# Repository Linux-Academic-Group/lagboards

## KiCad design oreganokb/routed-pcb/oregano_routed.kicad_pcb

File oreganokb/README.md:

# Oregano

[Upstream repo](https://github.com/pwlsp/oreganokb)

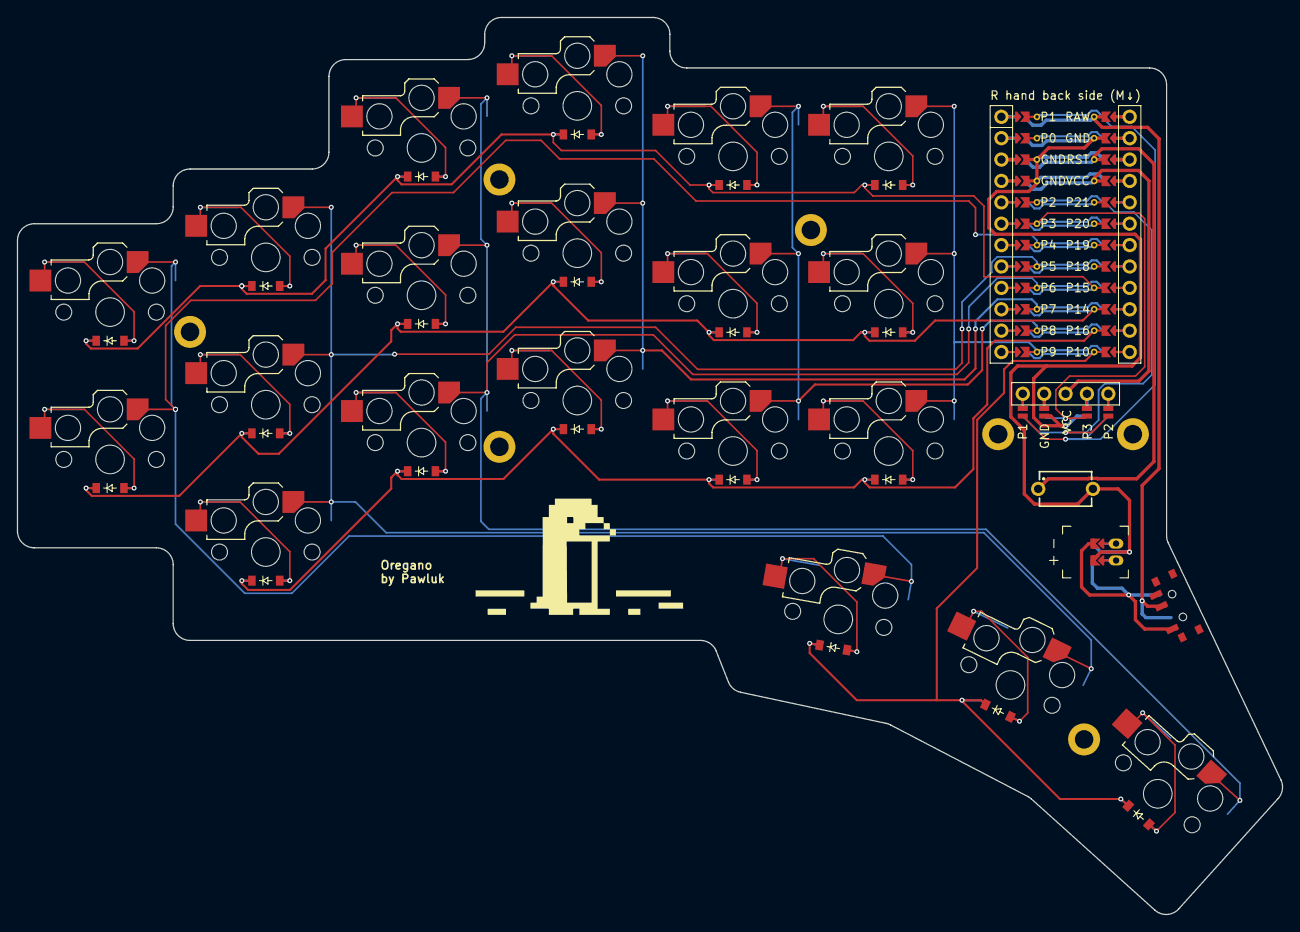
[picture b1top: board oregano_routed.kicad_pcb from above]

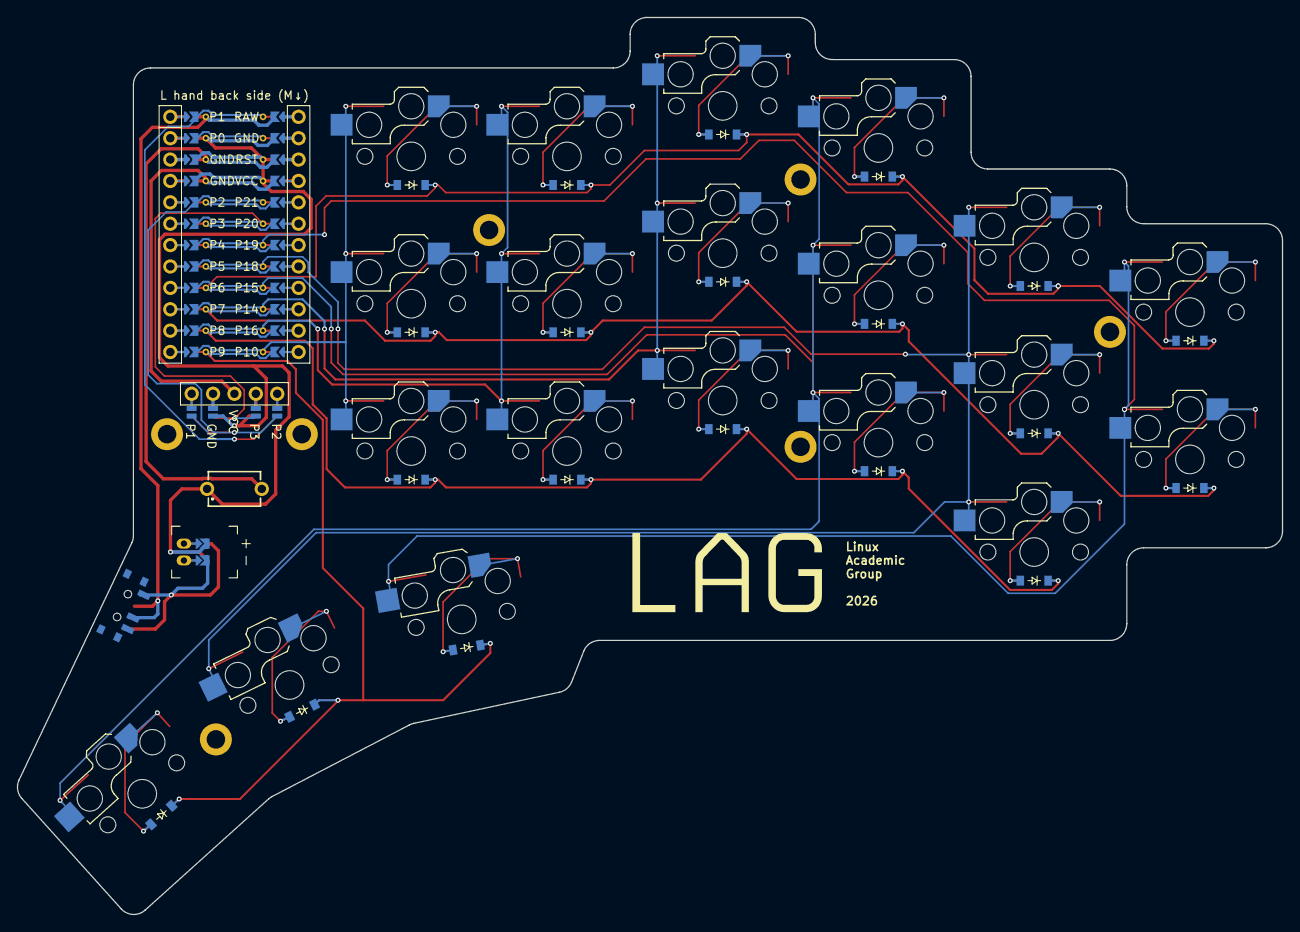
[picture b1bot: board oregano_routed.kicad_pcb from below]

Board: 2 copper layers, 150.3 x 106.6 mm, 52 parts (20 on the bottom side), 44 nets.

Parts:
D1, D2, D3, D4, D5, D6, D7, D8, D9, D10, D11, D12, D13, D14, D15, D16, D17, D18, D19, D20: diode_tht_sod123
DISP1: display_nice_view
H1, H2, H3, H4, H5, H6, H7: mounting_hole_plated
JST1: battery_connector_jst_ph_2
MCU1: mcu_supermini_nrf52840
S1, S2, S3, S4, S5, S6, S7, S8, S9, S10, S11, S12, S13, S14, S15, S16, S17, S18, S19, S20: switch_choc_v1_v2
S21: 434121025816
T1: SW_SPDT_PCM12

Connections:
BAT_P: JST1.1, T1.1
DISP1_1: DISP1.1, DISP1.14, DISP1.27
DISP1_2: DISP1.2, DISP1.15, DISP1.26
DISP1_4: DISP1.4, DISP1.16, DISP1.25
DISP1_5: DISP1.5, DISP1.17, DISP1.24
GND: DISP1.11, DISP1.21, JST1.2, MCU1.102, MCU1.121, MCU1.122, S21.2
JST1_1: JST1.11, JST1.21, JST1.31
JST1_2: JST1.12, JST1.22, JST1.32
P1: DISP1.10, DISP1.20, MCU1.124
P2: DISP1.13, DISP1.23, MCU1.120
P3: DISP1.12, DISP1.22, MCU1.119
P4: MCU1.118, S1.1, S1.2, S2.1, S2.2, S18.1, S18.2
P5: MCU1.117, S3.1, S3.2, S4.1, S4.2, S5.1, S5.2, S19.1, S19.2
P6: MCU1.116, S6.1, S6.2, S7.1, S7.2, S8.1, S8.2, S20.1, S20.2
P7: MCU1.115, S9.1, S9.2, S10.1, S10.2, S11.1, S11.2
P8: MCU1.114, S12.1, S12.2, S13.1, S13.2, S14.1, S14.2
P9: MCU1.113, S15.1, S15.2, S16.1, S16.2, S17.1, S17.2
P10: D18.1, D19.1, D20.1, MCU1.112
P14: D1.1, D4.1, D7.1, D10.1, D13.1, D16.1, MCU1.110
P15: D2.1, D5.1, D8.1, D11.1, D14.1, D17.1, MCU1.109
P16: D3.1, D6.1, D9.1, D12.1, D15.1, MCU1.111
RAW: MCU1.101, T1.2
RST: MCU1.103, S21.1
VCC: DISP1.3, MCU1.104
far_row: D20.2, S20.1, S20.2
home_row: D19.2, S19.1, S19.2
index_bottom: D12.2, S12.1, S12.2
index_home: D13.2, S13.1, S13.2
index_top: D14.2, S14.1, S14.2
inner_bottom: D15.2, S15.1, S15.2
inner_home: D16.2, S16.1, S16.2
inner_top: D17.2, S17.1, S17.2
middle_bottom: D9.2, S9.1, S9.2
middle_home: D10.2, S10.1, S10.2
middle_top: D11.2, S11.1, S11.2
near_row: D18.2, S18.1, S18.2
outer_home: D1.2, S1.1, S1.2
outer_top: D2.2, S2.1, S2.2
pinky_bottom: D3.2, S3.1, S3.2
pinky_home: D4.2, S4.1, S4.2
pinky_top: D5.2, S5.1, S5.2
ring_bottom: D6.2, S6.1, S6.2
ring_home: D7.2, S7.1, S7.2
ring_top: D8.2, S8.1, S8.2

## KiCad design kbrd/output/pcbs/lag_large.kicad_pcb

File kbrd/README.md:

```bash
ergogen . && flatpak --command=pcbnew run org.kicad.KiCad output/pcbs/lag_large.kicad_pcb                                                                                   
```

```
 encoder | 1    RAW | 
 encoder | 0    GND |
         | GND  RST |
         | GND  VCC |
     SDA | 2     21 | analog
     SCL | 3     20 | analog
   COL_5 | 4     19 | analog
   COL_4 | 5     18 | ROW_4
   COL_3 | 6     15 | ROW_3
   COL_2 | 7     14 | ROW_2
   COL_1 | 8     16 | ROW_1
   COL_0 | 9     10 | ROW_0
```

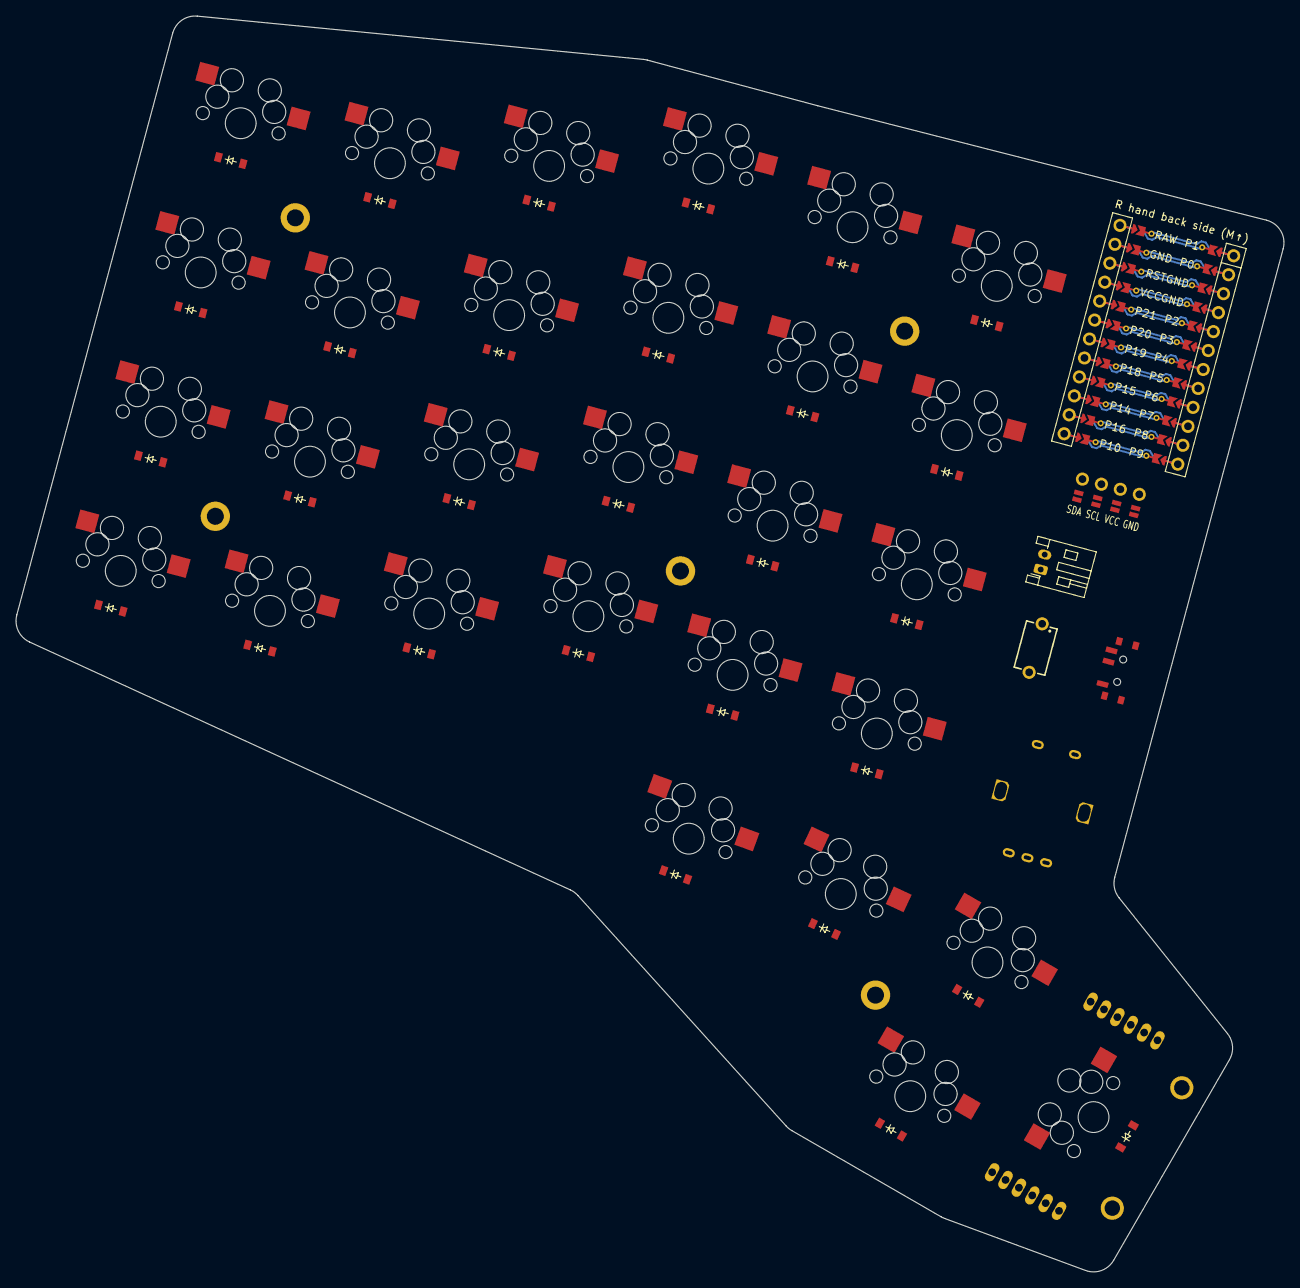
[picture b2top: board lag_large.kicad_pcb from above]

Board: 2 copper layers, 164.2 x 162.6 mm, 72 parts (1 on the bottom side), 57 nets.

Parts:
D1, D2, D3, D4, D5, D6, D7, D8, D9, D10, D11, D12, D13, D14, D15, D16, D17, D18, D19, D20, D21, D22, D23, D24, D25, D26, D27, D28, D29, D30: diode_tht_sod123
DISP1: nice!view
H1, H2, H3, H4, H5: mounting_hole_plated
MCU1: mcu_supermini_nrf52840
RE1: rotary_encoder_ec11_ec12
S1, S2, S3, S4, S5, S6, S7, S8, S9, S10, S11, S12, S13, S14, S15, S16, S17, S18, S19, S20, S21, S22, S23, S24, S25, S26, S27, S28, S29: MX
S30: 434121025816
T1: SW_SPDT_PCM12
XX1, XX2: joystick
_1: JST_PH_S2B-PH-K_1x02_P2.00mm_Horizontal

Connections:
DISP1_1: DISP1.4, DISP1.13, DISP1.20
DISP1_2: DISP1.3, DISP1.12, DISP1.21
DISP1_3: DISP1.2, DISP1.11, DISP1.22
DISP1_4: DISP1.1, DISP1.10, DISP1.23
GND: DISP1.14, DISP1.24, MCU1.103, MCU1.104, MCU1.123, RE1.B, S30.2, XX1.2, XX1.5, XX2.2, XX2.5, _1.1
P0: MCU1.102, RE1.A
P1: MCU1.101, RE1.C
P2: DISP1.17, DISP1.27, MCU1.105
P3: DISP1.16, DISP1.26, MCU1.106
P4: MCU1.107, S1.1, S2.1, S3.1, S4.1, S25.1
P5: MCU1.108, S5.1, S6.1, S7.1, S8.1, S26.1
P6: MCU1.109, S9.1, S10.1, S11.1, S12.1, S28.1
P7: MCU1.110, S13.1, S14.1, S15.1, S16.1, S27.1
P8: MCU1.111, S17.1, S18.1, S19.1, S20.1, S29.1
P9: MCU1.112, RE1.S1, S21.1, S22.1, S23.1, S24.1
P10: D25.1, D26.1, D27.1, D28.1, D29.1, D30.1, MCU1.113
P14: D2.1, D6.1, D10.1, D14.1, D18.1, D22.1, MCU1.115
P15: D3.1, D7.1, D11.1, D15.1, D19.1, D23.1, MCU1.116
P16: D1.1, D5.1, D9.1, D13.1, D17.1, D21.1, MCU1.114
P18: D4.1, D8.1, D12.1, D16.1, D20.1, D24.1, MCU1.117
P19: MCU1.118, XX1.4, XX2.4
P20: MCU1.119, XX1.3, XX2.3
P21: MCU1.120, XX1.6, XX2.6
RAW: MCU1.124, T1.2
RST: MCU1.122, S30.1
VCC: DISP1.15, DISP1.25, MCU1.121, XX1.1, XX2.1
en_s2: D30.2, RE1.S2
index_bottom: D17.2, S17.2
index_home: D18.2, S18.2
index_num: D20.2, S20.2
index_top: D19.2, S19.2
inner_bottom: D21.2, S21.2
inner_home: D22.2, S22.2
inner_num: D24.2, S24.2
inner_rowb: D29.2, S29.2
inner_rowt: D27.2, S27.2
inner_top: D23.2, S23.2
middle_bottom: D13.2, S13.2
middle_home: D14.2, S14.2
middle_num: D16.2, S16.2
middle_rowb: D28.2, S28.2
middle_rowt: D26.2, S26.2
middle_top: D15.2, S15.2
outer_bottom: D1.2, S1.2
outer_home: D2.2, S2.2
outer_num: D4.2, S4.2
outer_rowt: D25.2, S25.2
outer_top: D3.2, S3.2
pinky_bottom: D5.2, S5.2
pinky_home: D6.2, S6.2
pinky_num: D8.2, S8.2
pinky_top: D7.2, S7.2
ring_bottom: D9.2, S9.2
ring_home: D10.2, S10.2
ring_num: D12.2, S12.2
ring_top: D11.2, S11.2
sw1: T1.1, _1.2

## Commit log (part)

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2025-09-13 lag large kbrd
2025-10-25 footprint changes
2025-10-30 nix devShell for project
2025-11-13 joystick adjustments for ergofunctor
2025-11-18 change joystick model
2025-11-19 change joystick and finish config
2025-11-19 fix mcu-switchs connection
2025-11-20 fix connected columns
2025-11-20 joystick-button connection
2025-11-21 add switch traces
2025-11-21 added another keyboard
2025-11-22 added mcu jack and reset
2025-11-22 configured jack better
2025-11-23 unfinished update of joystick and switches
2025-11-24 add pcb routes
2025-11-24 add def kicad_pro to ergofunctor
2025-11-24 fix joystick
2025-11-24 fix path to diode
2025-11-24 added key net/matrix
2025-11-27 changes in routes and add gerber files
2025-11-28 added mounting holes
2025-11-28 fixed diodes
2025-11-29 routed the pcb
